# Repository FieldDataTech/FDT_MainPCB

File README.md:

# FDT_MainPCB
Eagle CADsoft files for Main Atmel based PCB

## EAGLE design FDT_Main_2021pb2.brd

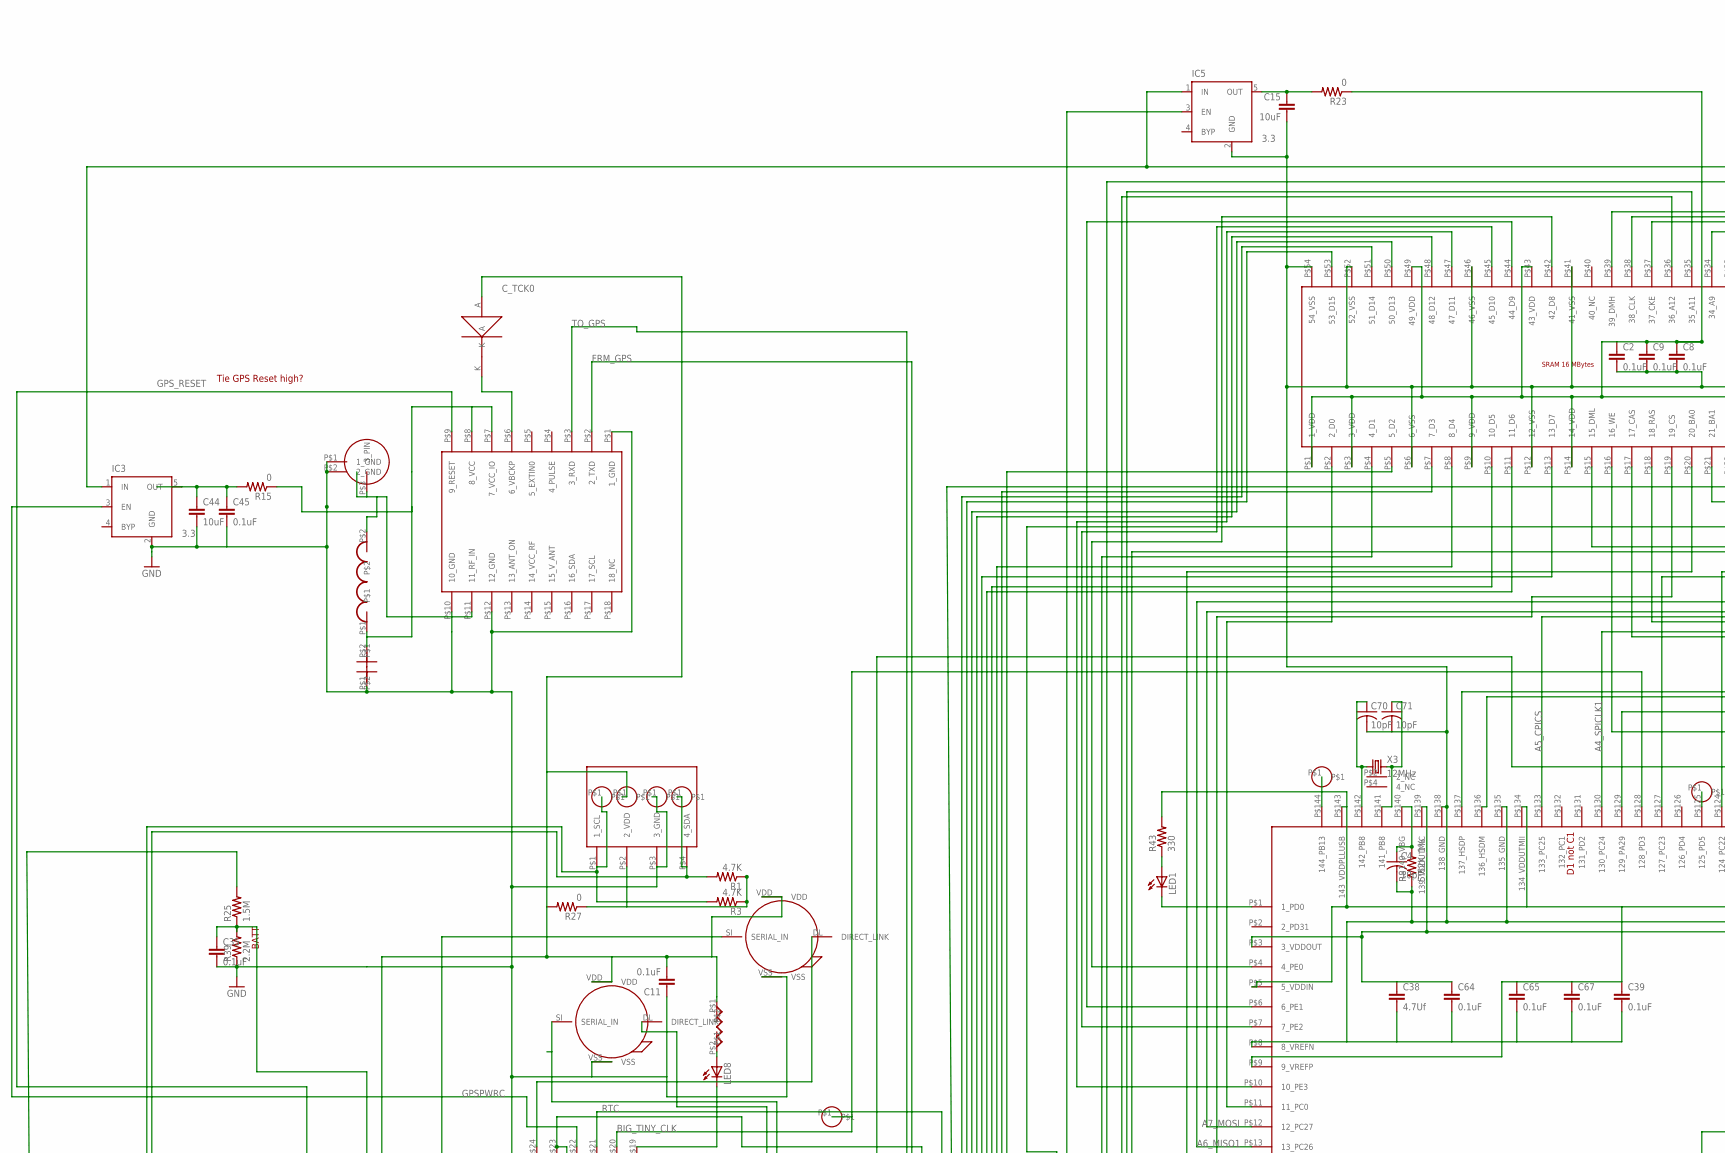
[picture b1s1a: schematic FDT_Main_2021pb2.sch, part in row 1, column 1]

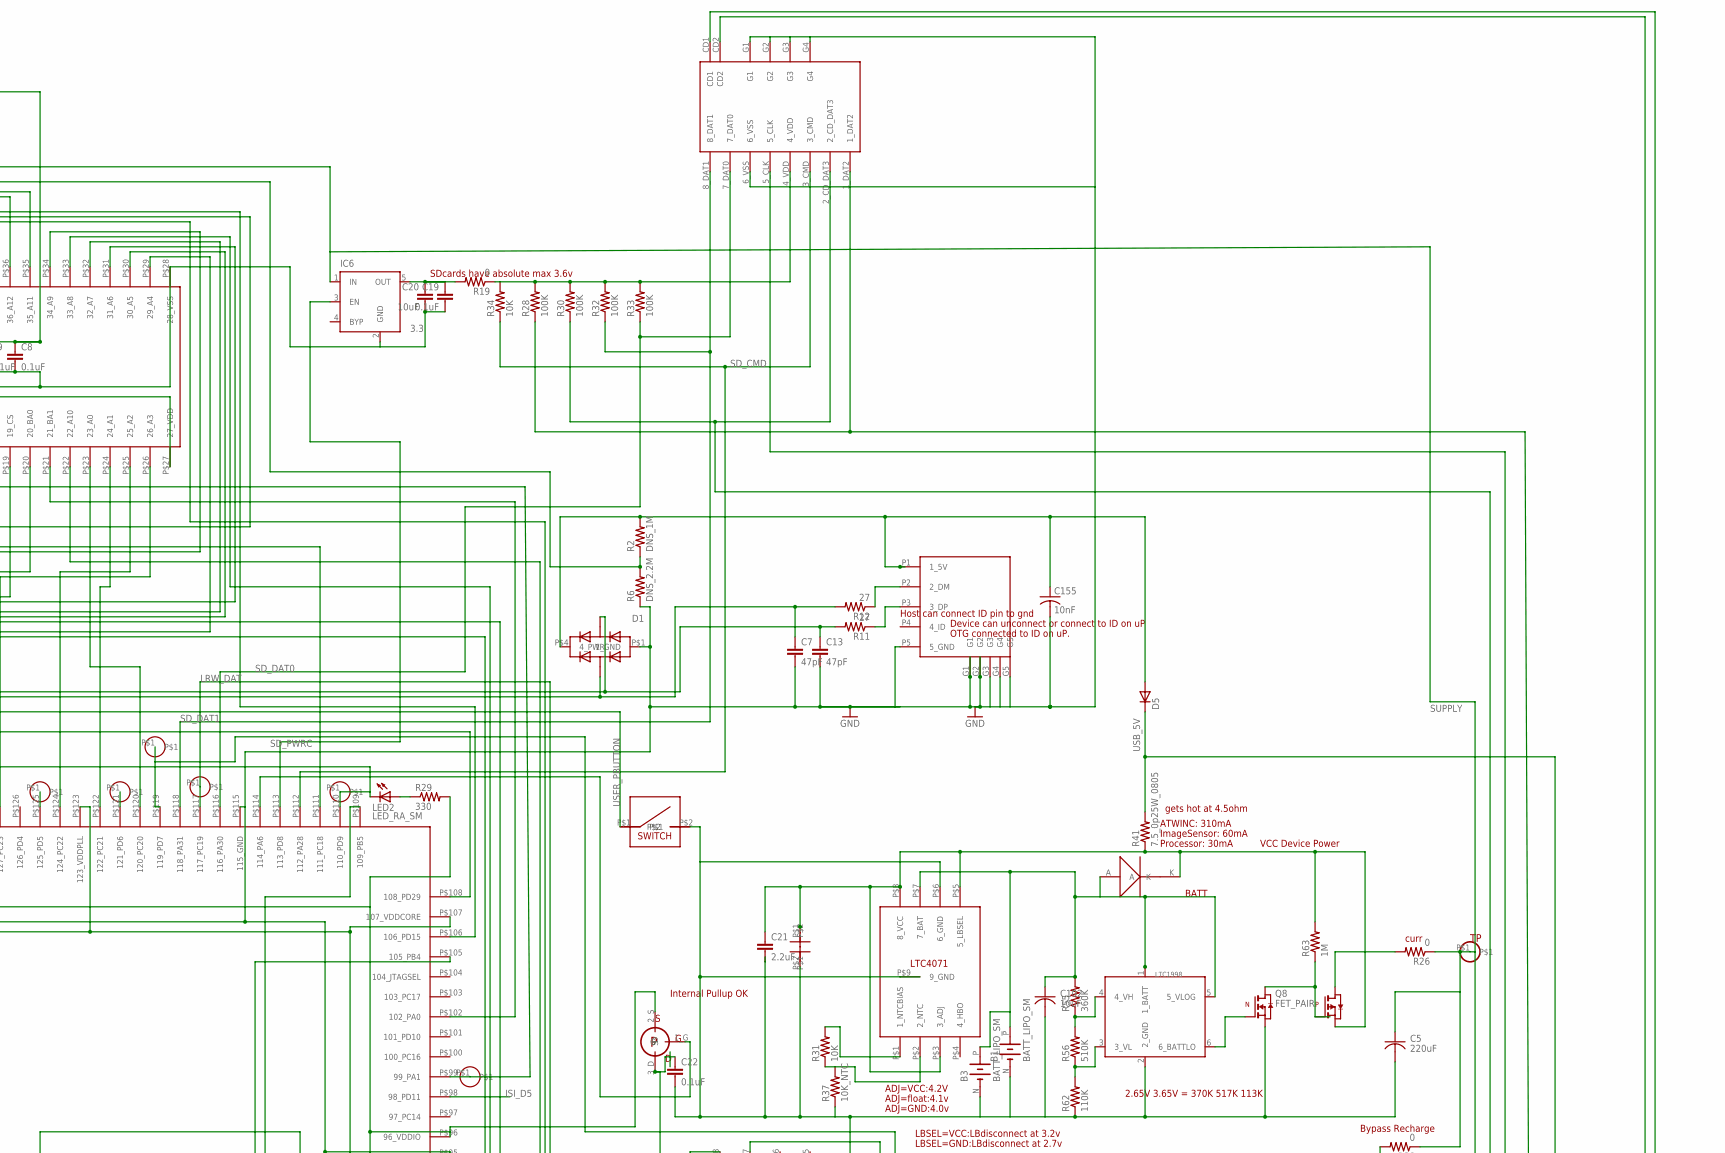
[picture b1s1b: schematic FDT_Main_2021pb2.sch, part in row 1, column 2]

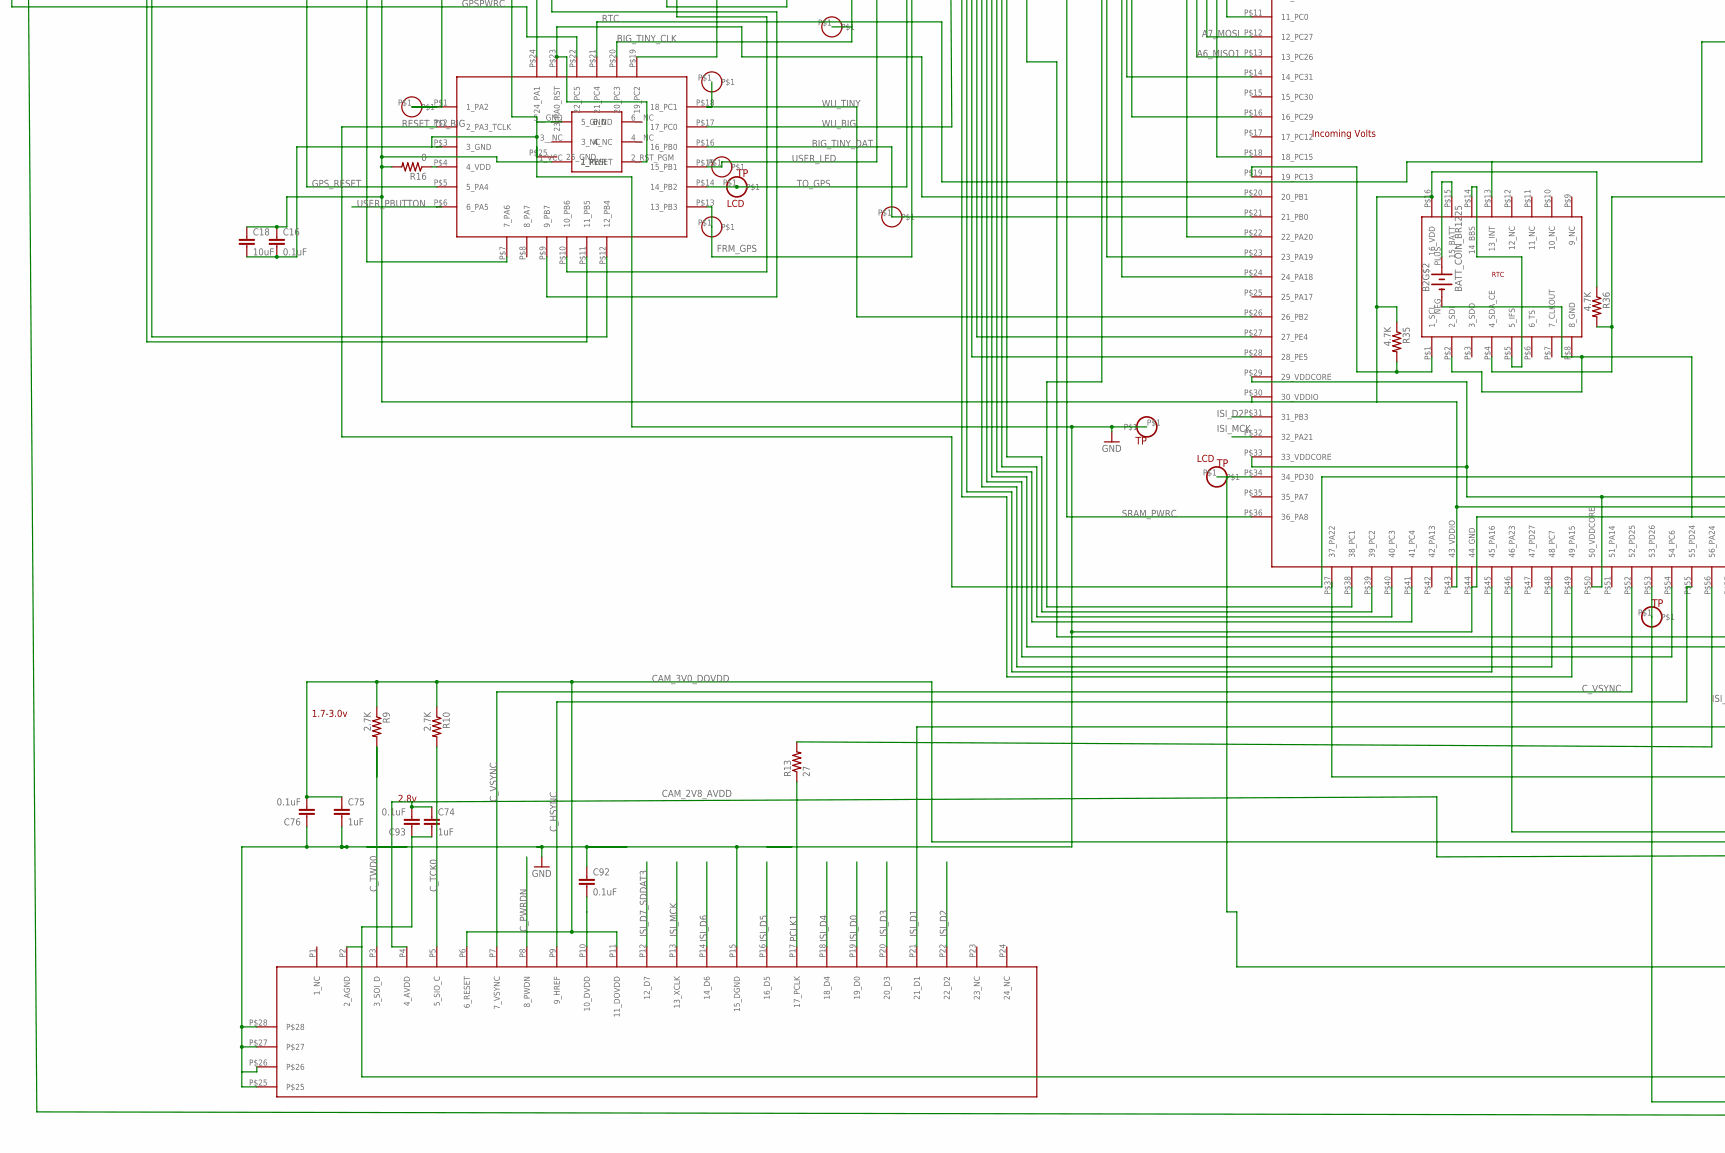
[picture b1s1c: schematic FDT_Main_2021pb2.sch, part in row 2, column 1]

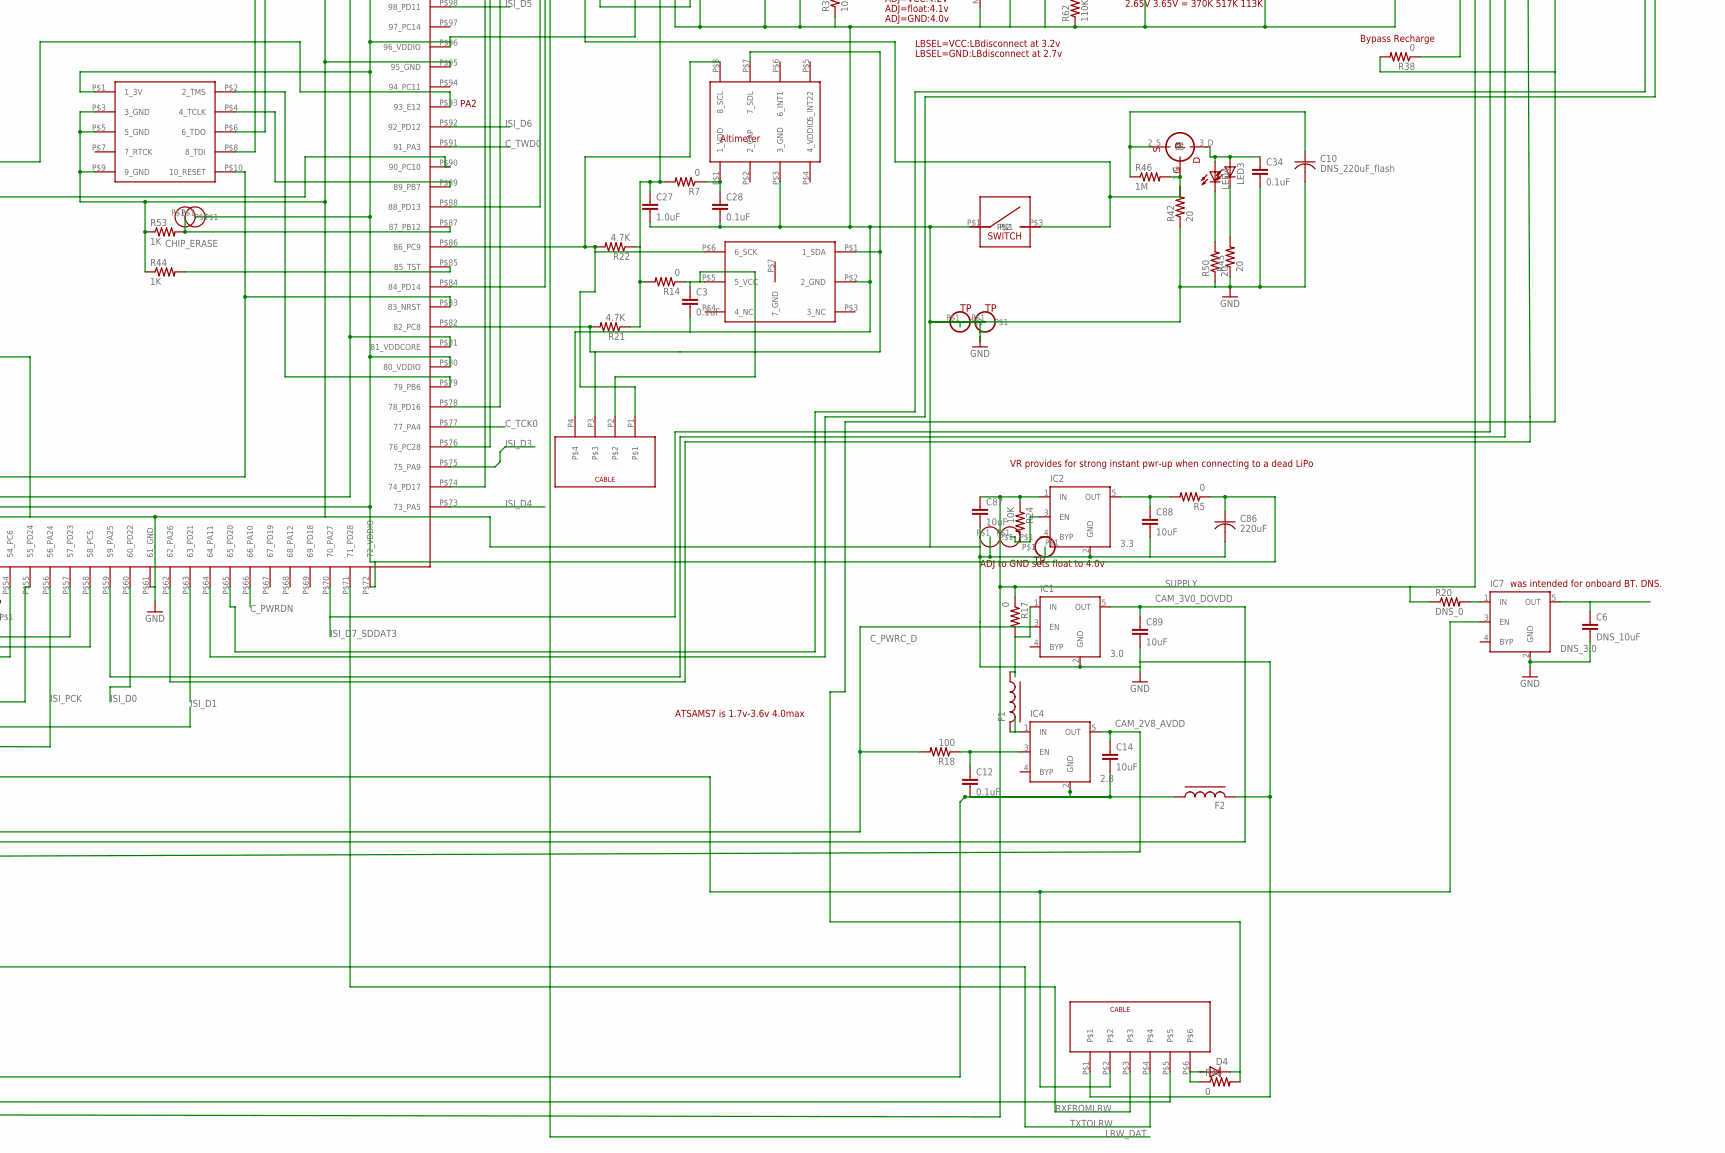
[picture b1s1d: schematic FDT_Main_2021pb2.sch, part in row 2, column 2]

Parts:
B1, B3: BATT_LIPO_SM
B2: BATT_COIN_BR1225
C2, C3, C8, C9, C11, C12, C16, C19, C22, C28, C34, C35, C39, C45, C64, C65, C67, C76, C92, C93: 0.1uF; C0402
C4, C70, C71: 10pF; SMD_0402
C5, C86: 220uF; C1210K
C6: DNS_10uF; C0603
C7, C13: 47pF; C0402
C10: DNS_220uF_flash; C1210K
C14, C15, C18, C20, C44, C87, C88, C89: 10uF; C0603
C21: 2.2uF; C0603
C27: 1.0uF; C0603
C29: 0.1uF; SMD_0402
C38: 4.7Uf; C0603
C43: 18pF; SMD_0402
C74, C75: 1uF; C0603
C102: 10uF; C0805ELEC
C155: 10nF; SMD_0402
D1: ESD_SM; TVSDIODE
D2, D3: DIO_SCH; SOD323
D4, D5: DIODE_SCHTKY; SOD323
F1, F2: FERRITE_0603; R0603
G2: GPS_ANT; GPS_ANTE
IC1: 3.0; SOT23-5
IC2, IC3, IC5, IC6: 3.3; SOT23-5
IC4: 2.8; SOT23-5
IC7: DNS_3.0; SOT23-5
J1: JTAG_KINETIS
J2: CONN_FPC_24P; CONN_FPC_24PIN
J3: MICRO_SD_HORIZ
J4: USB_MICRO_SMT; USB_MICRO_2019SMT
J5: HDR_PGM_TINY_SMT
J6: CONN_4PCABLE_VERT; CONN_4PCABLE
J7: CONN_6P_VERT; CONN_6PCABLE
L5: 100nH; SMD_IND
LED1, LED8: LEDCHIP-LED0603; CHIP-LED0603
LED2: LED_RA_SM
LED3, LED4: LED5MM
PIR1, PIR2: PIR_DUAL_4P; PIR_4P
Q1, Q5: MOSFET_P; SOT23_PFET
Q8: FET_PAIR; SSOT6
R1, R3, R21, R22, R35, R36: 4.7K; R0402
R2: DNS_1M; R0402
R5, R7, R14, R15, R16, R17, R19, R23, R26, R27, R38, R40: 0; R0402
R6: DNS_2.2M; R0402
R8: 5.62K_1%; R0402
R9, R10: 2.7K; SMD_0402
R11, R12: 27; R0402
R13: 27; SMD_0402
R18: 100; R0402
R20: DNS_0; R0402
R24, R31, R34: 10K; R0402
R25: 1.5M; R0402
R28, R30, R32, R33: 100K; R0402
R29, R43: 330; R0402
R37: 10K_NTC; R0402
R39: 2.2M; R0402
R41: 7.5_0p25W_0805; M0805
R42, R45, R50: 20; R0402
R44, R53: 1K; SMD_0402
R46, R63: 1M; R0402
R55: 360K; R0402
R56: 510K; R0402
R62: 110K; R0402
R65: 330; SMD_0402
SW1: SWITH_NO; SW_SQ
T2, T3, T4, T5, T6, T7, T12, T13: TESTP_SM
TP1, TP2, TP4, TP6, TP10, TP15, TP16, TP17, TP18, TP24, TP26, TP27, TP29: TP_SMT
TP3, TP5, TP7, TP8, TP9, TP11: TP_THSM
TP12, TP13: TP_THSM2
U1: ALTIMETER_NXP; ALTIMETER_MPL
U2: ATSAMV71_144; LQFP144
U4: HUMIDITY_A
U5: ALS
U6: RTC_2019; SOIC16_RTC
U7: SRAM_16M_2X16; TSOP_54
U9: LTC4071; MSOP_8
U11: UBLOX_M8
U19: LTC1998; SOT23-6L
U24: ATTINY_817_QFN; QFN24
U$1: SWITCH
X3: 12MHz; XTAL_SMALL

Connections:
A0: U2.P$120 (120_PC20), U7.P$23 (23_A0)
A1: U2.P$122 (122_PC21), U7.P$24 (24_A1)
A2: U2.P$124 (124_PC22), U7.P$25 (25_A2)
A3: U2.P$127 (127_PC23), U7.P$26 (26_A3)
A4_SPICLK1: U2.P$130 (130_PC24), U7.P$29 (29_A4)
A5_CPICS: U2.P$133 (133_PC25), U7.P$30 (30_A5)
A6_MISO1: U2.P$13 (13_PC26), U7.P$31 (31_A6)
A7_MOSI: U2.P$12 (12_PC27), U7.P$32 (32_A7)
A8: U2.P$76 (76_PC28), U7.P$33 (33_A8)
A9: U2.P$16 (16_PC29), U7.P$34 (34_A9)
A10: U2.P$88 (88_PD13), U7.P$22 (22_A10)
A11: U2.P$14 (14_PC31), U7.P$35 (35_A11)
A12: U2.P$24 (24_PA18), U7.P$36 (36_A12)
AGND: C12.2, C14.2, C74.2, C93.1, F2.1, IC4.2 (GND), J2.P2 (2_AGND)
ALT_PWRC: Q5.1_G (G), U2.P$114 (114_PA6)
BA0: U2.P$22 (22_PA20), U7.P$20 (20_BA0)
BATT: B1.P (+), B3.P (+), C102.1P, D3.A, R55.2, U9.P$7 (7_BAT), U19.1 (1_BATT), U19.5 (5_VLOG)
BATT1: C10.1 (1P), Q1.2_S (S), R46.1
BIG_TINY_CLK: TP29.P$1, U2.P$128 (128_PD3), U24.P$20 (20_PC3)
BIG_TINY_DAT: TP27.P$1, U2.P$21 (21_PB0), U24.P$16 (16_PB0)
CAM_2V8_AVDD: C14.1, C74.1, C93.2, IC4.5 (OUT), J2.P4 (4_AVDD)
CAM_3V0_DOVDD: C75.1, C76.2, C89.1, IC1.5 (OUT), J2.P6 (6_RESET), J2.P11 (11_DOVDD), R9.P$1 (1), R10.P$1 (1)
CARD_DETECT_A: J3.CD1, U2.P$64 (64_PA11)
CARD_DETECT_B: J3.CD2, U2.P$65 (65_PD20)
CAS: U2.P$74 (74_PD17), U7.P$17 (17_CAS)
CHIP_ERASE: R53.P$2 (2), TP7.P$1, U2.P$87 (87_PB12)
CK: U2.P$57 (57_PD23), U7.P$38 (38_CLK)
CKE: U2.P$84 (84_PD14), U7.P$37 (37_CKE)
CS: U2.P$18 (18_PC15), U7.P$19 (19_CS)
C_HSYNC: J2.P9 (9_HREF), U2.P$55 (55_PD24)
C_PWRC_D: IC1.3 (EN), R18.2, U2.P$46 (46_PA23)
C_PWRDN: J2.P8 (8_PWDN), U2.P$66 (66_PA10)
C_TCK0: J2.P5 (5_SIO_C), R10.P$2 (2), U2.P$77 (77_PA4)
C_TWD0: J2.P3 (3_SOI_D), R9.P$2 (2), U2.P$91 (91_PA3)
C_VSYNC: J2.P7 (7_VSYNC), U2.P$52 (52_PD25)
D0: U2.P$11 (11_PC0), U7.P$2 (2_D0)
D1: U2.P$38 (38_PC1), U7.P$4 (4_D1)
D2: U2.P$39 (39_PC2), U7.P$5 (5_D2)
D3: U2.P$40 (40_PC3), U7.P$7 (7_D3)
D4: U2.P$41 (41_PC4), U7.P$8 (8_D4)
D5: U2.P$58 (58_PC5), U7.P$10 (10_D5)
D6: U2.P$54 (54_PC6), U7.P$11 (11_D6)
D7: U2.P$48 (48_PC7), U7.P$13 (13_D7)
D8: U2.P$4 (4_PE0), U7.P$42 (42_D8)
D9: U2.P$6 (6_PE1), U7.P$44 (44_D9)
D10: U2.P$7 (7_PE2), U7.P$45 (45_D10)
D11: U2.P$10 (10_PE3), U7.P$47 (47_D11)
D12: U2.P$27 (27_PE4), U7.P$48 (48_D12)
D13: U2.P$28 (28_PE5), U7.P$50 (50_D13)
D14: U2.P$49 (49_PA15), U7.P$51 (51_D14)
D15: U2.P$45 (45_PA16), U7.P$53 (53_D15)
DISABLE_PWR: IC2.3 (EN), R24.2, TP13.P$1
DM: C7.1, D1.P$2 (2_S2), R12.2, U2.P$136 (136_HSDM)
DP: C13.1, D1.P$3 (3_S1), R11.2, U2.P$137 (137_HSDP)
DVDD_REF: C92.2, J2.P10 (10_DVDD)
FRM_GPS: TP2.P$1, U11.P$2 (2_TXD), U24.P$13 (13_PB3)
GND: B1.N (-), B2.NEG (-), B3.N (-), C2.2, C3.2, C4.P$2 (2), C5.2 (2N), C6.2, C7.2, C8.2, C9.2, C10.2 (2N), C11.1, C13.2, C15.2, C16.2, C18.2, C19.2, C20.2, C21.2, C22.2, C27.2, C28.2, C29.P$2, C34.2, C35.2, C38.2, C39.2, C43.P$1, C44.2, C45.2, C64.2, C65.2, C67.2, C70.P$2 (2), C71.P$2 (2), C76.1, C86.2 (2N), C87.2, C88.2, C89.2, C92.1, C102.2N, C155.P$2 (2), D1.P$1 (1_GND), F2.2, G2.P$1 (1_GND), G2.P$2 (2_GND), IC1.2 (GND), IC2.2 (GND), IC3.2 (GND), IC5.2 (GND), IC6.2 (GND), IC7.2 (GND), J1.P$3 (3_GND), J1.P$5 (5_GND), J1.P$9 (9_GND), J2.P15 (15_DGND), J2.P$25, J2.P$26, J2.P$27, J2.P$28, J3.6_VSS, J3.G1, J3.G2, J3.G3, J3.G4, J4.G1, J4.G2, J4.G3, J4.G4, J4.G5, J4.P5 (5_GND), J5.5__GND (5_GND), J6.P4, J7.P$1, PIR1.VSS, PIR2.VSS, Q8.5 (N_S), R6.1, R8.1, R37.1, R39.1, R42.1, R44.P$1 (1), R45.1, R50.1, R53.P$1 (1), R62.1, SW1.P$2, T2.P$1, T3.P$1, T5.P$1, T12.P$1, TP8.P$1, TP12.P$1, U1.P$3 (3_GND), U2.P$8 (8_VREFN), U2.P$44 (44_GND), U2.P$61 (61_GND), U2.P$95 (95_GND), U2.P$115 (115_GND), U2.P$135 (135_GND), U2.P$138 (138_GND), U4.P$2 (2_GND), U5.P$3 (3_GND), U6.P$2 (2_SDI), U6.P$8 (8_GND), U7.P$6 (6_VSS), U7.P$12 (12_VSS), U7.P$28 (28_VSS), U7.P$41 (41_VSS), U7.P$46 (46_VSS), U7.P$52 (52_VSS), U7.P$54 (54_VSS), U9.P$6 (6_GND), U9.P$9 (9_GND), U11.P$1 (1_GND), U11.P$10 (10_GND), U11.P$12 (12_GND), U19.2 (2_GND), U24.P$3 (3_GND), U24.P$25 (25_GND), U$1.P$1
GPS1: G2.P$3 (3_PIN), L5.P$2, U11.P$11 (11_RF_IN)
GPSPWRC: IC3.3 (EN), U24.P$22 (22_PC5)
GPS_RESET: U11.P$9 (9_RESET), U24.P$5 (5_PA4)
GPS_VCC_X: C43.P$2, L5.P$1, R15.1, U11.P$7 (7_VCC_IO), U11.P$8 (8_VCC)
ISI_D0: J2.P19 (19_D0), U2.P$60 (60_PD22)
ISI_D1: J2.P21 (21_D1), U2.P$63 (63_PD21)
ISI_D2: J2.P22 (22_D2), U2.P$31 (31_PB3)
ISI_D3: J2.P20 (20_D3), U2.P$75 (75_PA9)
ISI_D4: J2.P18 (18_D4), U2.P$73 (73_PA5)
ISI_D5: J2.P16 (16_D5), U2.P$98 (98_PD11)
ISI_D6: J2.P14 (14_D6), U2.P$92 (92_PD12)
ISI_D7_SDDAT3: J2.P12 (12_D7), J3.2_CD_DAT3, R30.1, U2.P$70 (70_PA27)
ISI_MCK: J2.P13 (13_XCLK), U2.P$32 (32_PA21)
ISI_PCK: R13.P$2 (2), U2.P$56 (56_PA24)
LDM: U2.P$111 (111_PC18), U7.P$15 (15_DML)
LED: LED1.C, U2.P$1 (1_PD0)
LRW_DAT: TP1.P$1, U2.P$117 (117_PC19)
LRW_PWRC: IC7.3 (EN), J7.P$2, U2.P$37 (37_PA22)
unnamed: U6.P$5 (5_IFS), U6.P$14 (14_BBS)
unnamed: U2.P$102 (102_PA0), U7.P$21 (21_BA1)
unnamed: D4.2_A (A), J7.P$6, R40.1
unnamed: J5.2_RST_PGM (2_RESET), U2.P$20 (20_PB1), U24.P$23 (23_PA0_RST)
unnamed: J1.P$4 (4_TCLK), U2.P$89 (89_PB7)
unnamed: C44.1, C45.1, IC3.5 (OUT), R15.2
unnamed: J1.P$8 (8_TDI), U2.P$105 (105_PB4)
unnamed: J1.P$6 (6_TDO), U2.P$109 (109_PB5)
unnamed: J1.P$2 (2_TMS), U2.P$79 (79_PB6)
unnamed: C88.1, IC2.5 (OUT), R5.2
unnamed: C6.1, IC7.5 (OUT)
unnamed: R16.1, U24.P$4 (4_VDD)
unnamed: LED2.1_A (A), R29.1
unnamed: F1.1, IC1.1 (IN), R17.2
unnamed: C19.1, C20.1, IC6.5 (OUT), R19.2
unnamed: C15.1, IC5.5 (OUT), R23.2
unnamed: LED1.A, R43.1
unnamed: D2.K, U11.P$6 (6_VBCKP)
unnamed: PIR1.SI (SERIAL_IN), TP6.P$1, U24.P$1 (1_PA2)
unnamed: C38.1, C64.1, U2.P$3 (3_VDDOUT), U2.P$29 (29_VDDCORE), U2.P$33 (33_VDDCORE), U2.P$50 (50_VDDCORE), U2.P$81 (81_VDDCORE), U2.P$107 (107_VDDCORE), U2.P$123 (123_VDDPLL), U2.P$139 (139_VDDUTMIC)
unnamed: C70.P$1 (1), U2.P$142 (142_PB8), X3.P$1 (1_XTAL)
unnamed: C71.P$1 (1), U2.P$141 (141_PB8), X3.P$3 (3_XTAL)
unnamed: C4.P$1 (1), R8.2, U2.P$140 (140_VBG)
unnamed: C35.1, R25.1, R39.2, U24.P$7 (7_PA6)
unnamed: J3.4_VDD, R19.1, R28.2, R30.2, R32.2, R33.2, R34.2
unnamed: J7.P$5, T7.P$1, U2.P$53 (53_PD26)
unnamed: PIR1.DL (DIRECT_LINK), U24.P$24 (24_PA1)
unnamed: R35.2, U2.P$19 (19_PC13), U6.P$1 (1_SCL)
unnamed: C34.1, LED3.A, LED4.A, Q1.3_D (D)
unnamed: C22.1, C27.1, Q5.3_D (D), R7.2, R14.2, R21.1, R22.1
unnamed: J4.P2 (2_DM), R12.1
unnamed: TP17.P$1, U2.P$121 (121_PD6)
unnamed: R36.2, U2.P$90 (90_PC10), U6.P$4 (4_SDA_CE)
unnamed: TP10.P$1, U2.P$144 (144_PB13)
unnamed: R2.1, R6.2, U2.P$23 (23_PA19)
unnamed: C12.1, IC4.3 (EN), R18.1
unnamed: J4.P3 (3_DP), R11.1
unnamed: TP15.P$1, U2.P$125 (125_PD5)
unnamed: C28.1, R7.1, U1.P$1 (1_VDD)
unnamed: R44.P$2 (2), U2.P$85 (85_TST)
unnamed: C155.P$1 (1), D1.P$4 (4_PWR), D5.2_A (A), J4.P1 (1_5V), R2.2
unnamed: F1.2, IC4.1 (IN)
unnamed: U2.P$106 (106_PD15), U7.P$39 (39_DMH)
unnamed: IC7.1 (IN), R20.2
unnamed: R31.2, U9.P$1 (1_NTCBIAS)
unnamed: B2.PLUS (+), U6.P$15 (15_BATT)
unnamed: Q1.1_G (G), R42.2, R46.2, TP16.P$1, U2.P$119 (119_PD7), U$1.P$3
unnamed: R31.1, R37.2, U9.P$2 (2_NTC)
unnamed: LED3.K (C), R45.2
unnamed: LED4.K (C), R50.2
unnamed: LED8.C, U24.P$19 (19_PC2)
unnamed: LED8.A, R65.P$2
unnamed: R55.1, R56.2, U19.4 (4_VH)
unnamed: PIR2.SI (SERIAL_IN), U24.P$9 (9_PB7)
unnamed: R56.1, R62.2, U19.3 (3_VL)
unnamed: Q8.1 (N_G), U19.6 (6_BATTLO)
unnamed: Q8.3 (P_G), Q8.6 (N_D), R63.1
unnamed: PIR2.DL (DIRECT_LINK), U24.P$10 (10_PB6)
PCLK1: J2.P17 (17_PCLK), R13.P$1 (1)
RAS: U2.P$78 (78_PD16), U7.P$18 (18_RAS)
RESET_TO_BIG: J1.P$10 (10_RESET), U2.P$83 (83_NRST), U24.P$2 (2_PA3_TCLK)
RTC: U2.P$93 (93_E12), U6.P$13 (13_INT), U24.P$21 (21_PC4)
RXFROMLRW: J7.P$3, U2.P$71 (71_PD28)
SCL: J6.P1, R22.2, U1.P$8 (8_SCL), U2.P$86 (86_PC9), U4.P$6 (6_SCK)
SDA: J6.P3, R21.2, U1.P$7 (7_SDL), U2.P$82 (82_PC8), U4.P$1 (1_SDA)
SD_CLK: J3.5_CLK, U2.P$59 (59_PA25)
SD_CMD: J3.3_CMD, R34.1, U2.P$112 (112_PA28)
SD_DAT0: J3.7_DAT0, R33.1, U2.P$116 (116_PA30)
SD_DAT1: J3.8_DAT1, R32.1, U2.P$118 (118_PA31)
SD_DAT2: J3.1_DAT2, R28.1, U2.P$62 (62_PA26)
SD_PWRC: IC6.3 (EN), U2.P$113 (113_PD8)
SENSPWR: R1.1, R3.1, R27.1, U5.P$2 (2_VDD)
SENS_PWR: C3.1, J6.P2, R14.1, U4.P$5 (5_VCC)
SRAMPWR: C2.1, C8.1, C9.1, R23.1, U7.P$1 (1_VDD), U7.P$3 (3_VDD), U7.P$9 (9_VDD), U7.P$14 (14_VDD), U7.P$27 (27_VDD), U7.P$43 (43_VDD), U7.P$49 (49_VDD)
SRAM_PWRC: IC5.3 (EN), U2.P$36 (36_PA8)
SUPPLY: C5.1 (1P), C87.1, IC2.1 (IN), IC3.1 (IN), IC5.1 (IN), IC6.1 (IN), R17.1, R20.1, R24.1, R25.2, R26.1, R38.1, T13.P$1
TO_GPS: T6.P$1, U11.P$3 (3_RXD), U24.P$14 (14_PB2)
TXTOLRW: J7.P$4, T4.P$1, U2.P$34 (34_PD30)
T_SCL: R3.2, TP3.P$1, U5.P$1 (1_SCL), U24.P$11 (11_PB5)
T_SDA: R1.2, TP11.P$1, U5.P$4 (4_SDA), U24.P$12 (12_PB4)
USB_5V: D4.1_K (K), D5.1_K (K), R38.2, R40.2, R41.2
USER_LED: LED2.2_K (C), TP4.P$1, TP18.P$1, U2.P$110 (110_PD9), U24.P$15 (15_PB1)
USER_PBUTTON: SW1.P$1, U2.P$129 (129_PA29), U24.P$6 (6_PA5)
VCC: C11.2, C16.1, C18.1, C39.1, C65.1, C67.1, C86.1 (1P), D2.A, J1.P$1 (1_3V), J5.1_VCC (1_PWR), PIR1.VDD, PIR2.VDD, Q5.2_S (S), R5.1, R16.2, R27.2, R29.2, R35.1, R36.1, R43.2, R65.P$1, TP5.P$1, TP9.P$1, U2.P$5 (5_VDDIN), U2.P$9 (9_VREFP), U2.P$30 (30_VDDIO), U2.P$43 (43_VDDIO), U2.P$72 (72_VDDIO), U2.P$80 (80_VDDIO), U2.P$96 (96_VDDIO), U2.P$134 (134_VDDUTMII), U2.P$143 (143_VDDPLLUSB), U6.P$16 (16_VDD)
VCC1: C21.1, C29.P$1, D3.K, Q8.2 (P_S), R41.1, R63.2, U9.P$3 (3_ADJ), U9.P$5 (5_LBSEL), U9.P$8 (8_VCC)
VCC9: Q8.4 (P_D), R26.2
WE: U2.P$108 (108_PD29), U7.P$16 (16_WE)
WU_BIG: TP24.P$1, U2.P$99 (99_PA1), U24.P$17 (17_PC0)
WU_TINY: TP26.P$1, U2.P$26 (26_PB2), U24.P$18 (18_PC1)

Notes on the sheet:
ATSAMS7 is 1.7v-3.6v 4.0max
ADJ to GND sets float to 4.0v
VR provides for strong instant pwr-up when connecting to a dead LiPo
LCD
2.8v
1.7-3.0v
D1 not C1
Altimeter
PA2
Incoming Volts
BATT
SDcards have absolute max 3.6v
Tie GPS Reset high?
Internal Pullup OK
ADJ=VCC:4.2V
ADJ=float:4.1v
ADJ=GND:4.0v
LBSEL=GND:LBdisconnect at 2.7v
LBSEL=VCC:LBdisconnect at 3.2v
curr
ATWINC: 310mA
ImageSensor: 60mA
Processor: 30mA
gets hot at 4.5ohm
2.65V 3.65V = 370K 517K 113K
VCC Device Power
Host can connect ID pin to gnd
Device can unconnect or connect to ID on uP
OTG connected to ID on uP.
Bypass Recharge
was intended for onboard BT. DNS.

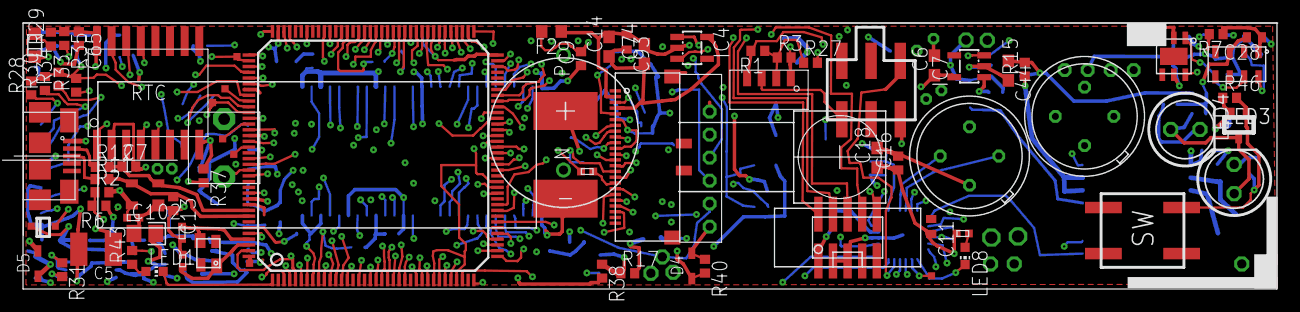
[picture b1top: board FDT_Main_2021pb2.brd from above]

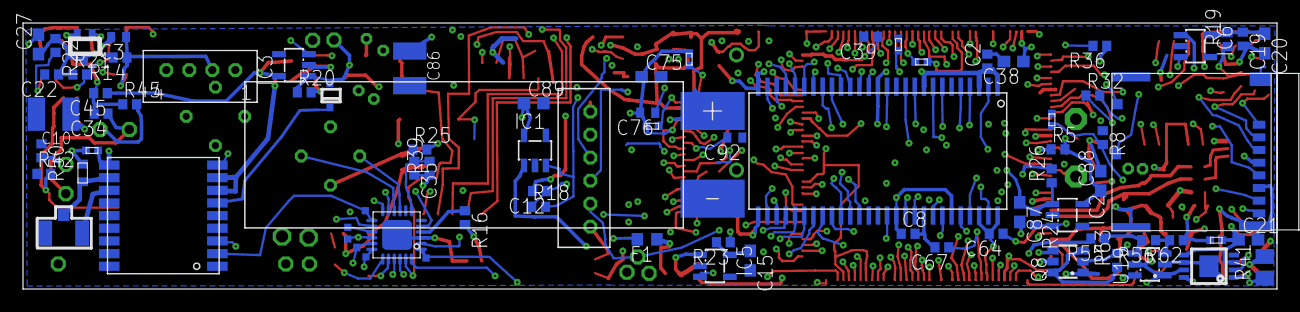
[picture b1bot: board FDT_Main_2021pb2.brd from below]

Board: 6 copper layers, 109.0 x 23.1 mm, 176 parts (83 on the bottom side), 164 nets.

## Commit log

2021-04-23 Original commit of Eagle CADsoft for Main Atmel based PCB
